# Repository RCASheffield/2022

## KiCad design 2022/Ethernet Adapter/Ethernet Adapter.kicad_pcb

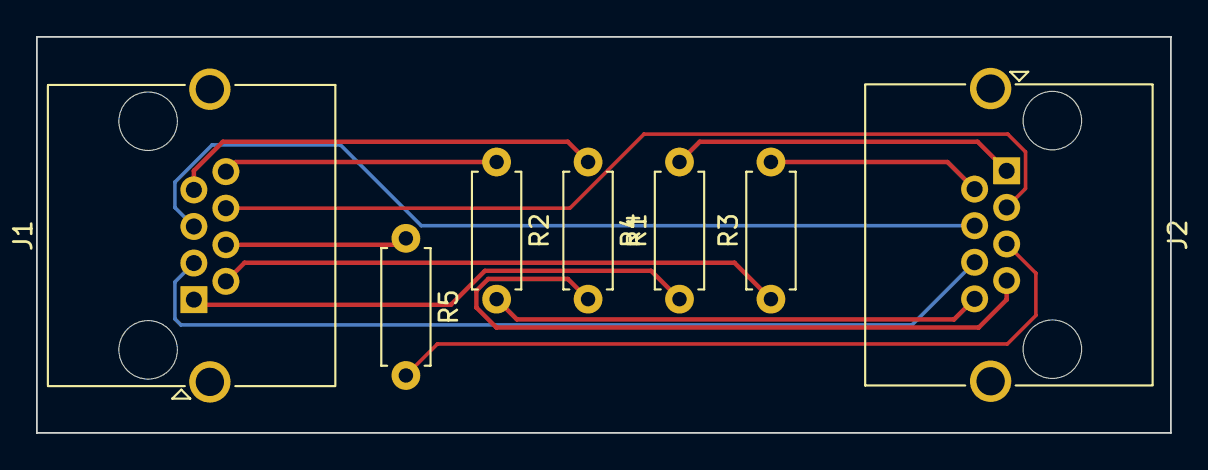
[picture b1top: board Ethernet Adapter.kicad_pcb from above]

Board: 2 copper layers, 63.0 x 22.0 mm, 7 parts (0 on the bottom side), 13 nets.

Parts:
J1, J2: Conn_01x08; RJ45_Amphenol_RJHSE5380
R1, R2, R3, R4, R5: Resistor; R_Axial_DIN0207_L6.3mm_D2.5mm_P7.62mm_Horizontal

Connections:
/GND: J2.7, R4.2
/INTERLOCK_IN: J2.2, R3.2
/INTERLOCK_RET: J2.8, R2.2
/POWER_EN: J2.1, R1.2
/RX+: J1.5, J2.4
/RX-: J2.5, R5.2
/TX+: J1.3, J2.6
/TX-: J1.6, J2.3
unnamed: J1.2, R3.1
unnamed: J1.4, R5.1
unnamed: J1.7, R4.1
unnamed: J1.8, R2.1
unnamed: J1.1, R1.1

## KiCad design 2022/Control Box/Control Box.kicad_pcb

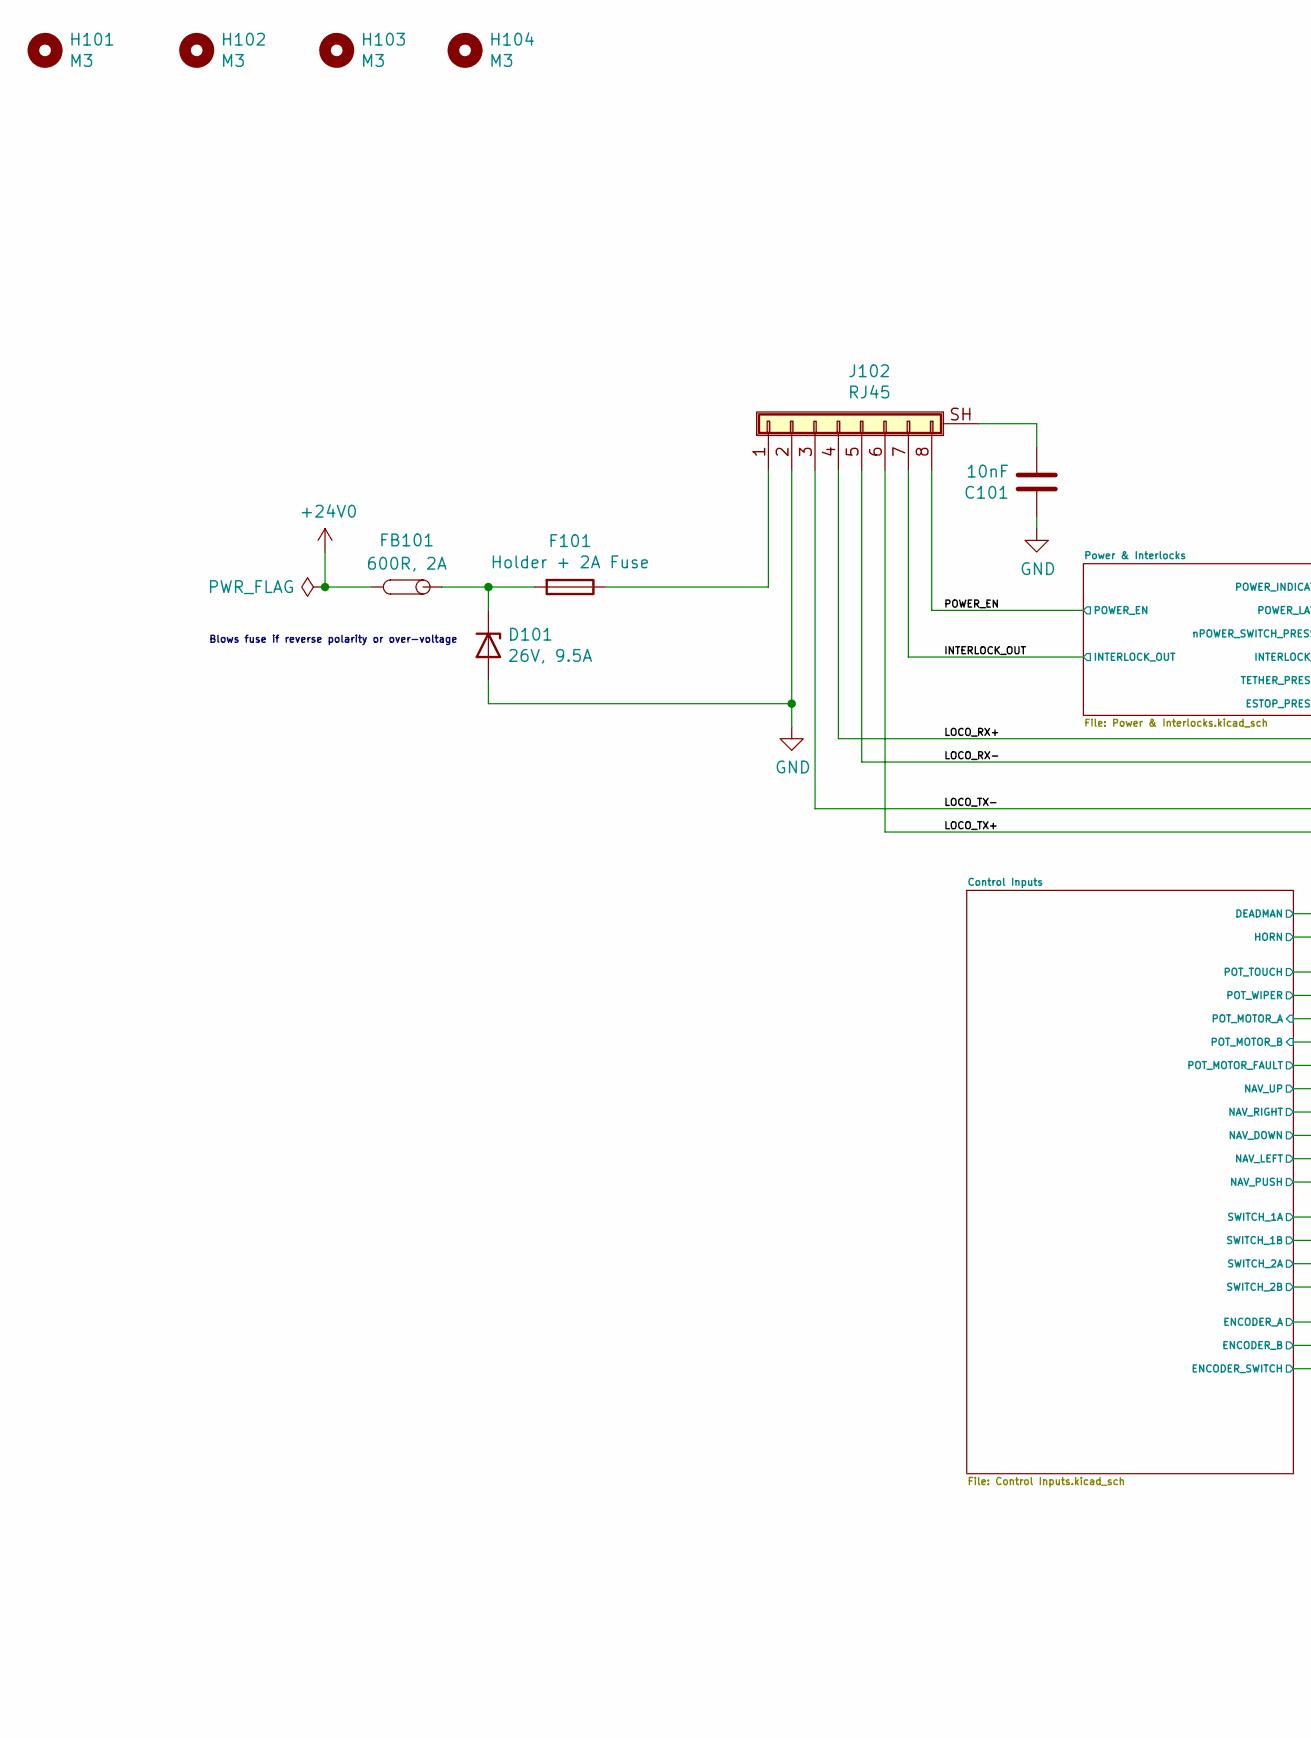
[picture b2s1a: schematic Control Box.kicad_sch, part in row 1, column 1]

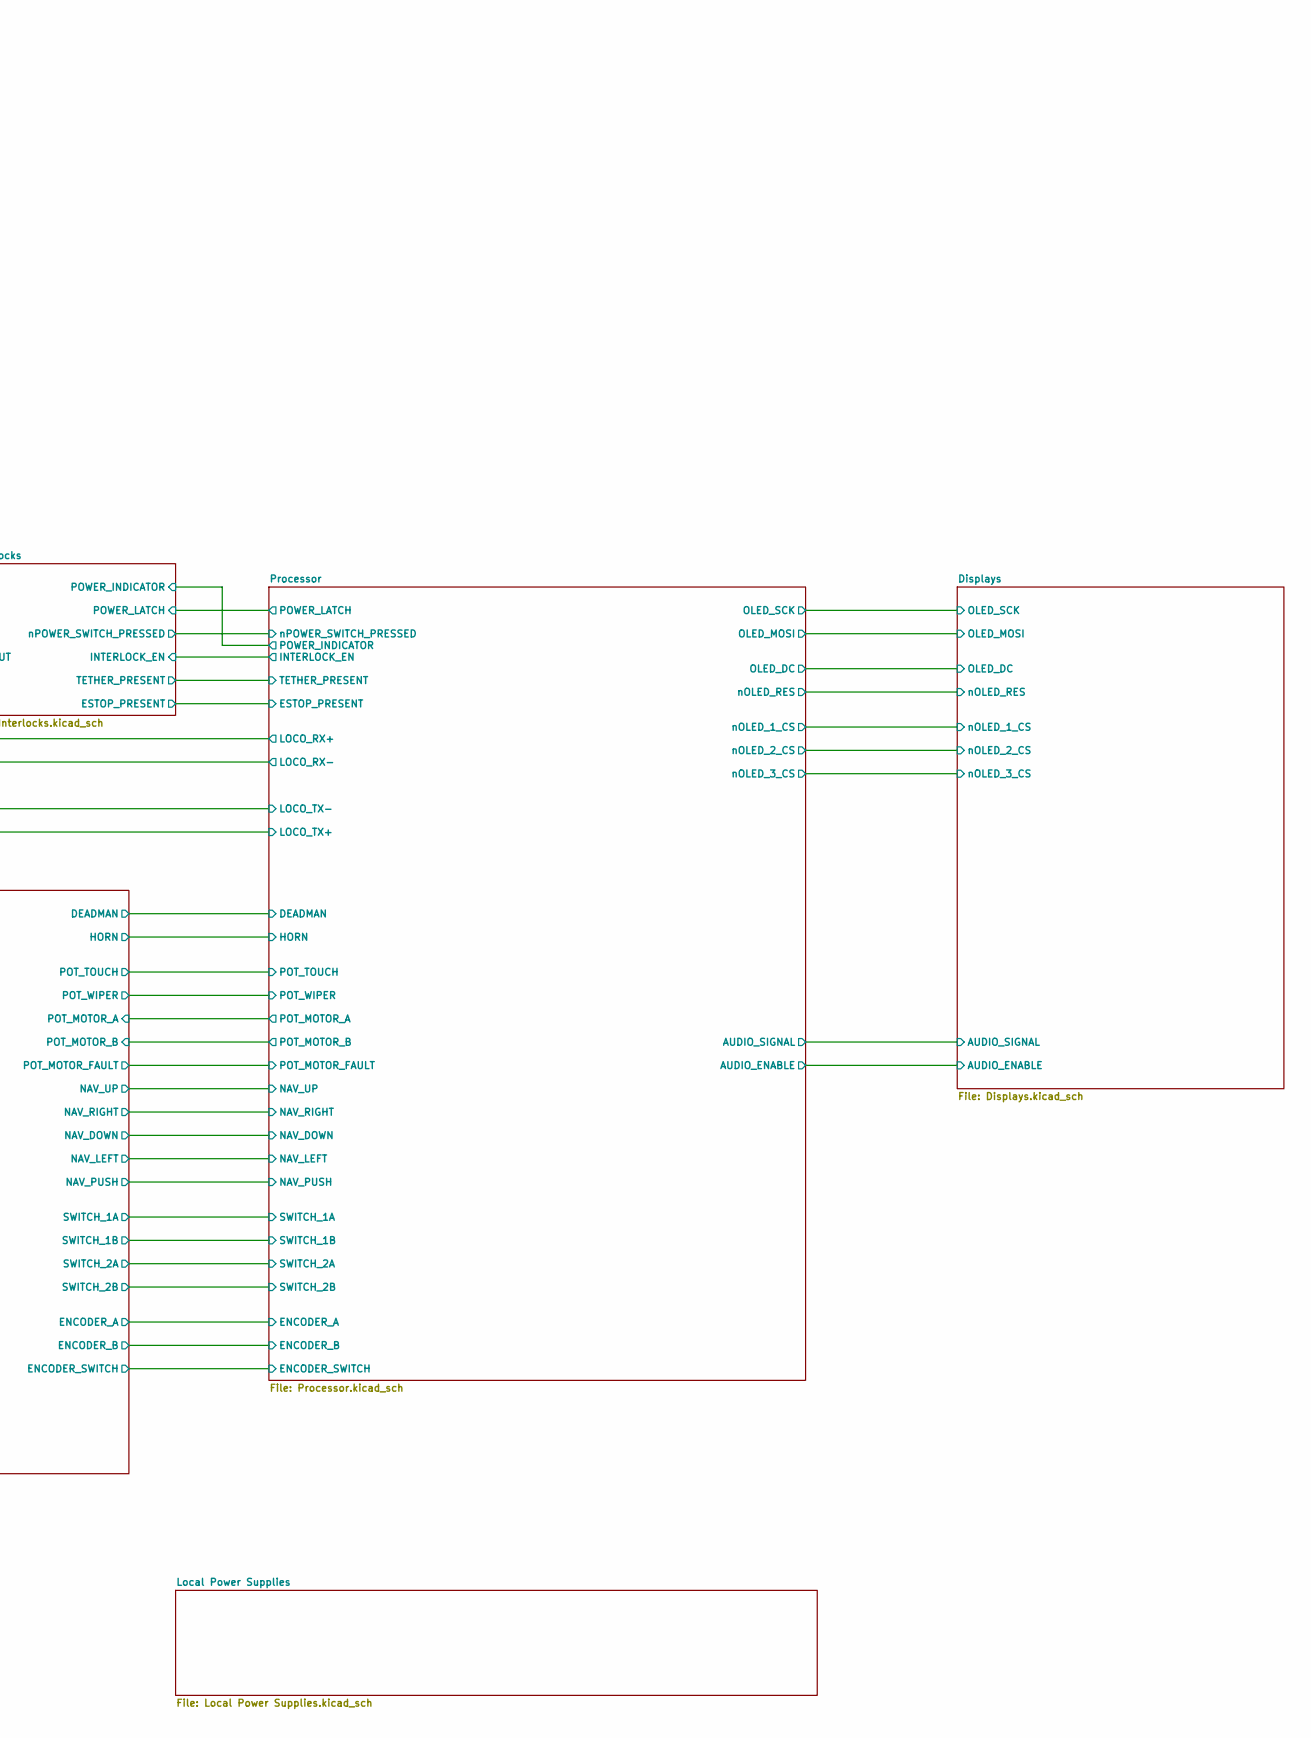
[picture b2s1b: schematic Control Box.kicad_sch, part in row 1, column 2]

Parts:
C101: 10nF; C_0603_1608Metric_Pad1.05x0.95mm_HandSolder; LCSC C57112
D101: 26V, 9.5A; D_SMA; Manufacturer Part Number SMAJ26A; LCSC C49370
F101: Holder + 2A Fuse; Fuseholder_Littelfuse_154; Manufacturer Part Number 0154002.DR
FB101: 600R, 2A; L_0805_2012Metric_Pad1.15x1.40mm_HandSolder; Manufacturer Part Number 74279220601
H101, H102, H103, H104: M3; MountingHole_3.2mm_M3
J102: RJ45; RJ45_Amphenol_RJHSE5380; Manufacturer Part Number RJHSE-5380

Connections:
+24V: FB101.2; also elsewhere on the board
/INTERLOCK_OUT: J102.7; also elsewhere on the board
/LOCO_RX+: J102.4; also elsewhere on the board
/LOCO_RX-: J102.5; also elsewhere on the board
/LOCO_TX+: J102.6; also elsewhere on the board
/LOCO_TX-: J102.3; also elsewhere on the board
/POWER_EN: J102.8; also elsewhere on the board
GND: C101.1, D101.2 (A), J102.2; also elsewhere on the board
unnamed: C101.2, J102.SH (Shield)
unnamed: D101.1 (K), F101.2, FB101.1
unnamed: F101.1, J102.1

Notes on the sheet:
Blows fuse if reverse polarity or over-voltage

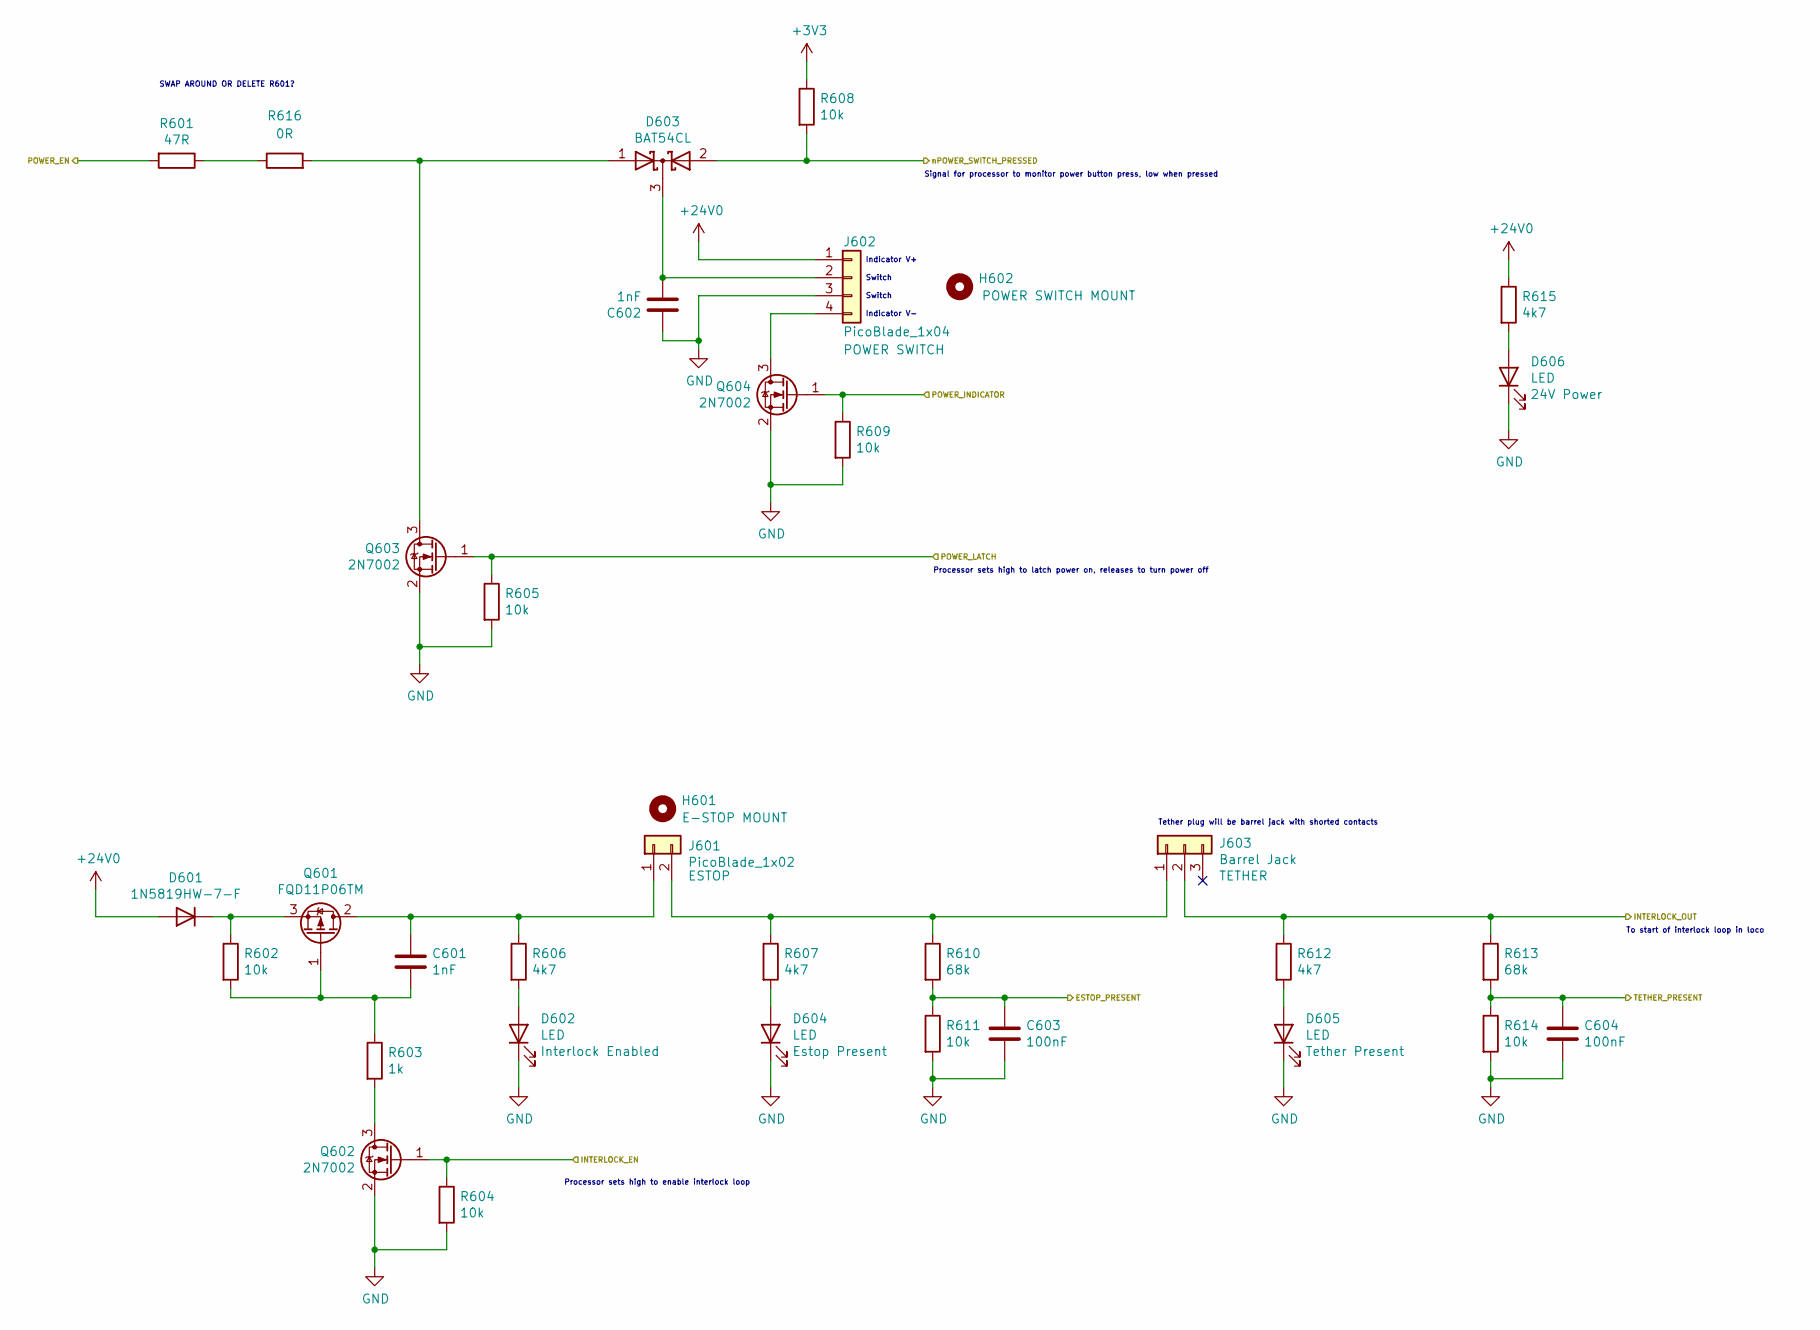
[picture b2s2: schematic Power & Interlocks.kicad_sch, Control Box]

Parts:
C601, C602: 1nF; C_0603_1608Metric_Pad1.05x0.95mm_HandSolder; LCSC C1588
C603, C604: 100nF; C_0603_1608Metric_Pad1.05x0.95mm_HandSolder; LCSC C14663
D601: 1N5819HW-7-F; D_SOD-123; Manufacturer Part Number 1N5819HW-7-F; LCSC C117948
D602, D604, D605: LED; LED_0603_1608Metric_Pad1.05x0.95mm_HandSolder; Manufacturer Part Number 150060YS75000; LCSC C205443
D603: BAT54CL; SOT-23_Handsoldering; Manufacturer Part Number BAT54CLT1G; LCSC C14308
D606: LED; LED_0603_1608Metric_Pad1.05x0.95mm_HandSolder; Manufacturer Part Number 150060VS75000; LCSC C2286
H601: 16mm Hole; 16mm_E-STOP
H602: 16mm Hole; 16mm_Power_Button
J601: PicoBlade_1x02; Molex_PicoBlade_53047-0210_1x02_P1.25mm_Vertical; Manufacturer Part Number 0530470210
J602: PicoBlade_1x04; Molex_PicoBlade_53047-0410_1x04_P1.25mm_Vertical
J603: Barrel Jack; BarrelJack_Wuerth_6941xx301002; Manufacturer Part Number 694106301002
Q601: FQD11P06TM; TO-252-2; Manufacturer Part Number FQD11P06TM; LCSC C165227
Q602, Q603, Q604: 2N7002; SOT-23_Handsoldering; Manufacturer Part Number 2N7002,215; LCSC C239589
R601: 47R; R_0603_1608Metric_Pad1.05x0.95mm_HandSolder; LCSC C23182
R602, R604, R605, R608, R609: 10k; R_0603_1608Metric_Pad1.05x0.95mm_HandSolder; LCSC C25804
R603: 1k; R_0603_1608Metric_Pad1.05x0.95mm_HandSolder; LCSC C21190
R606, R607, R612, R615: 4k7; R_0603_1608Metric_Pad1.05x0.95mm_HandSolder; LCSC C23162
R610, R613: 68k; R_0603_1608Metric_Pad1.05x0.95mm_HandSolder; LCSC C25804
R611, R614: 10k; R_0603_1608Metric_Pad1.05x0.95mm_HandSolder; LCSC C23231
R616: 0R

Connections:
+3V3: R608.1; also elsewhere on the board
+24V: D601.2 (A), J602.1, R615.1; also elsewhere on the board
/INTERLOCK_OUT: J603.2, R612.1, R613.1; also elsewhere on the board
/POWER_EN: R601.2; also elsewhere on the board
/Power & Interlocks/ESTOP_PRESENT: C603.1, R610.2, R611.1; also elsewhere on the board
/Power & Interlocks/INTERLOCK_EN: Q602.1 (G), R604.1; also elsewhere on the board
/Power & Interlocks/POWER_INDICATOR: Q604.1 (G), R609.1; also elsewhere on the board
/Power & Interlocks/POWER_LATCH: Q603.1 (G), R605.1; also elsewhere on the board
/Power & Interlocks/TETHER_PRESENT: C604.1, R613.2, R614.1; also elsewhere on the board
/Power & Interlocks/nPOWER_SWITCH_PRESSED: D603.2 (A), R608.2; also elsewhere on the board
GND: C602.1, C603.2, C604.2, D602.1 (K), D604.1 (K), D605.1 (K), D606.1 (K), J602.3, Q602.2 (S), Q603.2 (S), Q604.2 (S), R604.2, R605.2, R609.2, R611.2, R614.2; also elsewhere on the board
unnamed: C601.1, J601.1, Q601.2 (D), R606.1
unnamed: C601.2, Q601.1 (G), R602.2, R603.1
unnamed: C602.2, D603.3 (K), J602.2
unnamed: D601.1 (K), Q601.3 (S), R602.1
unnamed: D602.2 (A), R606.2
unnamed: D604.2 (A), R607.2
unnamed: D605.2 (A), R612.2
unnamed: D606.2 (A), R615.2
unnamed: J601.2, J603.1, R607.1, R610.1
unnamed: J602.4, Q604.3 (D)
unnamed: Q602.3 (D), R603.2

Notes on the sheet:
Switch
Processor sets high to enable interlock loop
To start of interlock loop in loco
SWAP AROUND OR DELETE R601?
Indicator V-
Processor sets high to latch power on, releases to turn power off
Signal for processor to monitor power button press, low when pressed
Tether plug will be barrel jack with shorted contacts
Indicator V+

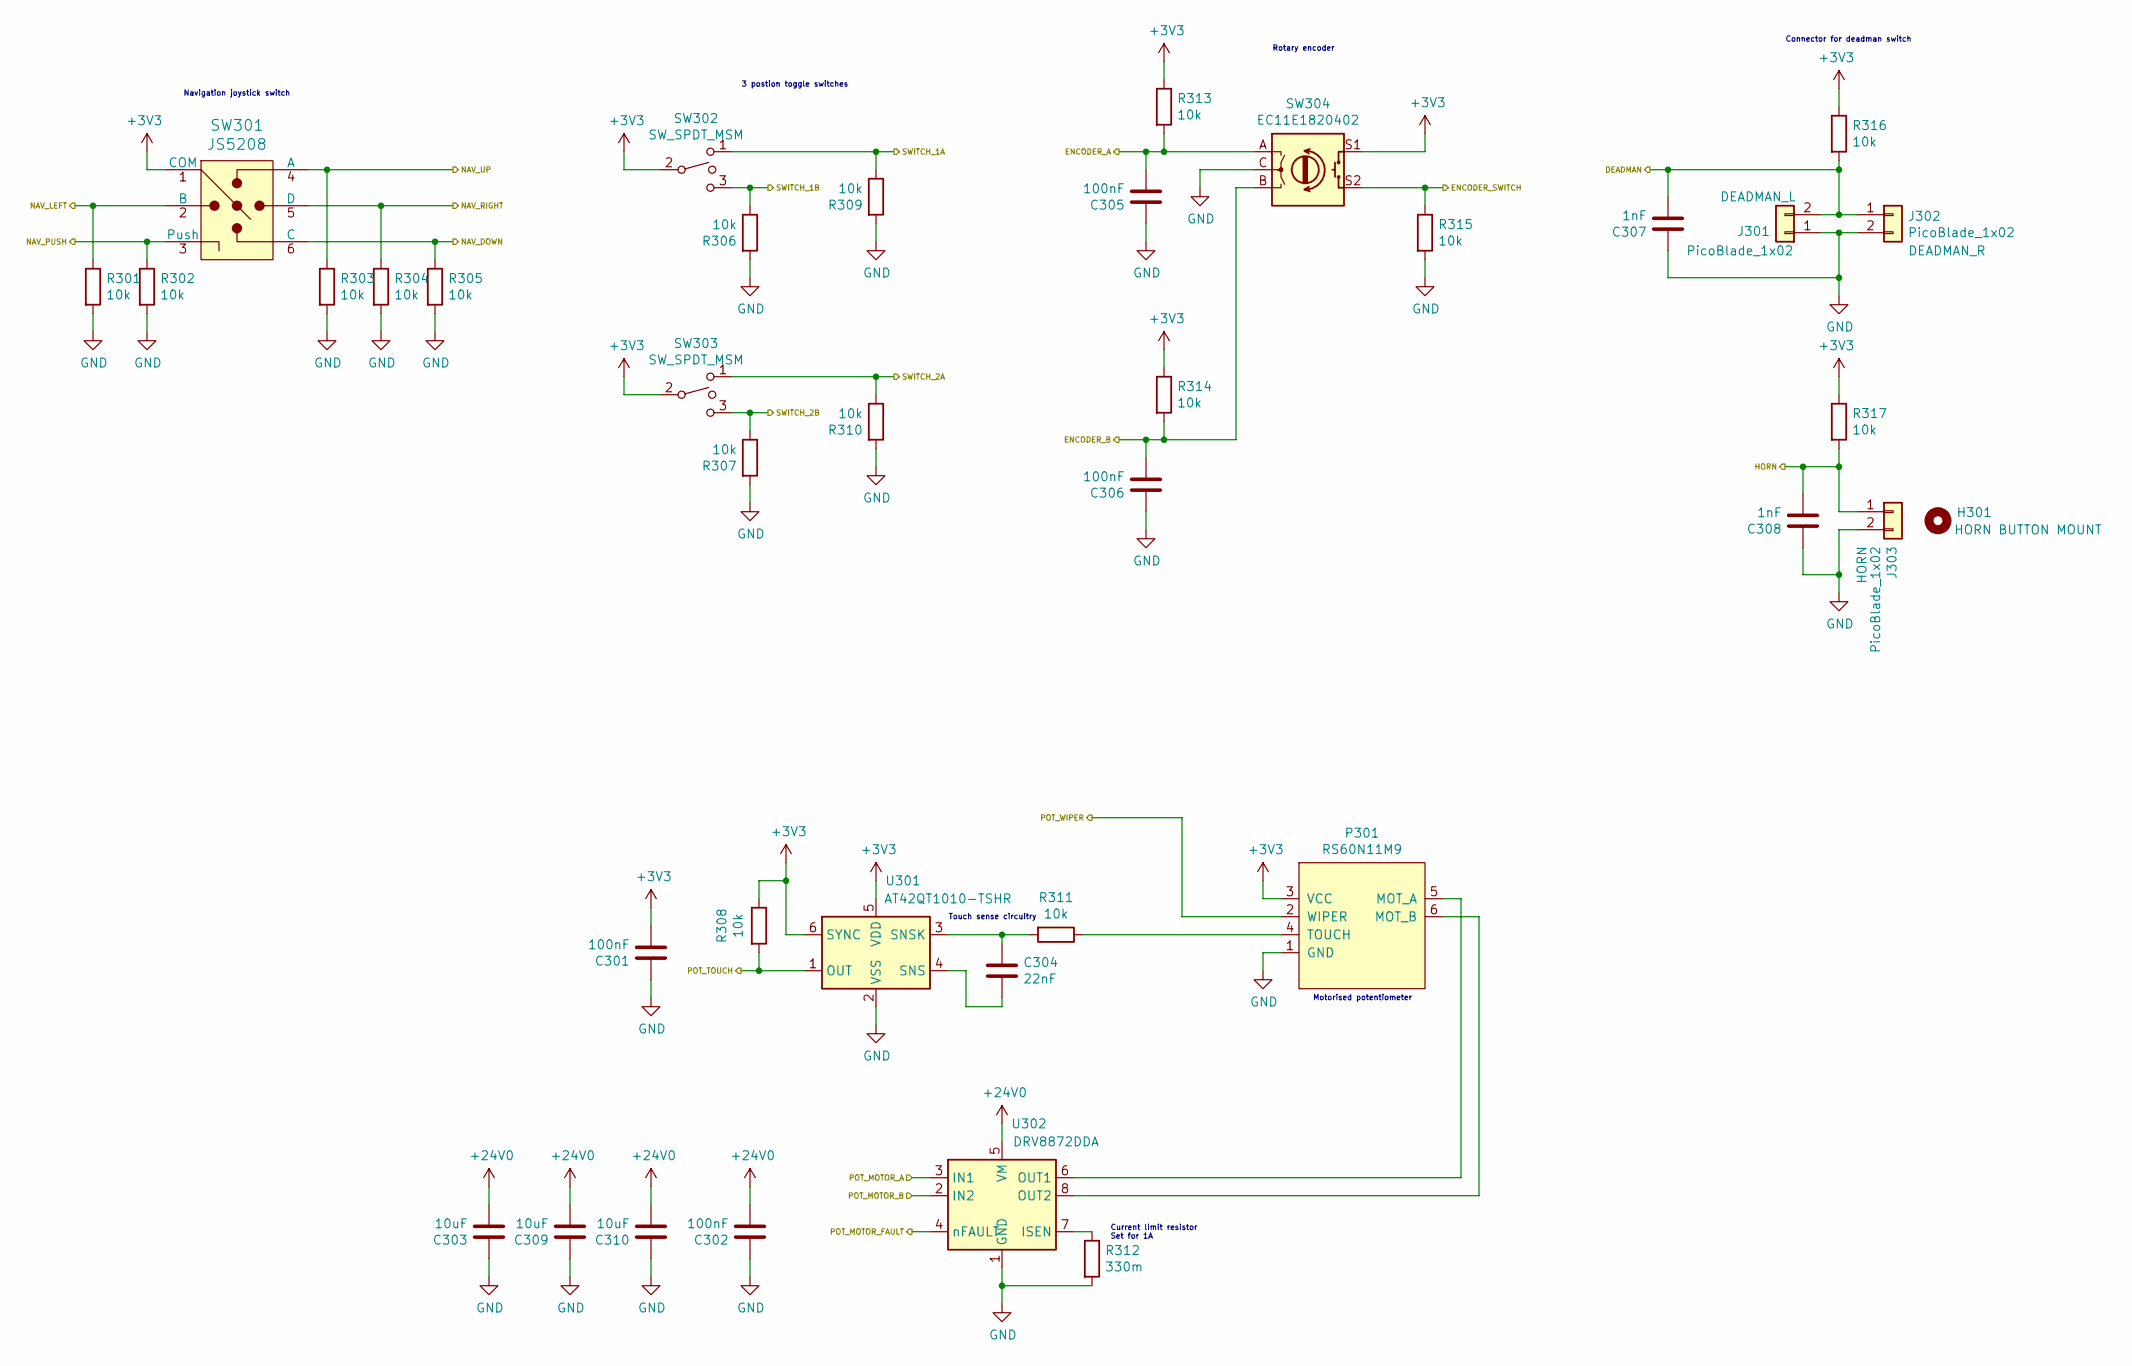
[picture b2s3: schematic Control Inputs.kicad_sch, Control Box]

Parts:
C301, C302, C305, C306: 100nF; C_0603_1608Metric_Pad1.05x0.95mm_HandSolder; LCSC C14663
C303, C309, C310: 10uF; C_1210_3225Metric_Pad1.42x2.65mm_HandSolder; LCSC C39232
C304: 22nF; C_0603_1608Metric_Pad1.05x0.95mm_HandSolder; LCSC C21122
C307, C308: 1nF; C_0603_1608Metric_Pad1.05x0.95mm_HandSolder; LCSC C1588
H301: 16mm Hole; 16mm_Blank_Button
J301, J302, J303: PicoBlade_1x02; Molex_PicoBlade_53047-0210_1x02_P1.25mm_Vertical; Manufacturer Part Number 0530470210
P301: RS60N11M9; Potentiometer_Motorised_RS60N11M9
R301, R302, R303, R304, R305, R306, R307, R308, R309, R310, R311, R313, R314, R315, R316, R317: 10k; R_0603_1608Metric_Pad1.05x0.95mm_HandSolder; LCSC C25804
R312: 330m; R_1210_3225Metric_Pad1.42x2.65mm_HandSolder; LCSC C127712
SW301: JS5208; Switch_Nav_12.4x12.4mm
SW302, SW303: SW_SPDT_MSM; SW_Toggle_14x7mm
SW304: EC11E1820402; RotaryEncoder_Alps_EC11E-Switch_Vertical_H20mm
U301: AT42QT1010-TSHR; SOT-23-6; LCSC C74512
U302: DRV8872DDA; Texas_HTSOP-8-1EP_3.9x4.9mm_P1.27mm_EP2.95x4.9mm_Mask2.4x3.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; LCSC C114179

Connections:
+3V3: C301.2, P301.3 (VCC), R308.1, R313.1, R314.1, R316.1, R317.1, SW301.1 (COM), SW302.2, SW303.2, SW304.S1, U301.5 (VDD), U301.6 (SYNC); also elsewhere on the board
+24V: C302.2, C303.1, C309.1, C310.1, U302.5 (VM); also elsewhere on the board
/Control Inputs/DEADMAN: C307.2, J301.2, J302.1, R316.2; also elsewhere on the board
/Control Inputs/ENCODER_A: C305.2, R313.2, SW304.A; also elsewhere on the board
/Control Inputs/ENCODER_B: C306.2, R314.2, SW304.B; also elsewhere on the board
/Control Inputs/ENCODER_SWITCH: R315.1, SW304.S2; also elsewhere on the board
/Control Inputs/HORN: C308.2, J303.1, R317.2; also elsewhere on the board
/Control Inputs/NAV_DOWN: R305.1, SW301.6 (C); also elsewhere on the board
/Control Inputs/NAV_LEFT: R301.1, SW301.2 (B); also elsewhere on the board
/Control Inputs/NAV_PUSH: R302.1, SW301.3 (Push); also elsewhere on the board
/Control Inputs/NAV_RIGHT: R304.1, SW301.5 (D); also elsewhere on the board
/Control Inputs/NAV_UP: R303.1, SW301.4 (A); also elsewhere on the board
/Control Inputs/POT_MOTOR_A: U302.3 (IN1); also elsewhere on the board
/Control Inputs/POT_MOTOR_B: U302.2 (IN2); also elsewhere on the board
/Control Inputs/POT_MOTOR_FAULT: U302.4 (nFAULT); also elsewhere on the board
/Control Inputs/POT_TOUCH: R308.2, U301.1 (OUT); also elsewhere on the board
/Control Inputs/POT_WIPER: P301.2 (WIPER); also elsewhere on the board
/Control Inputs/SWITCH_1A: R309.1, SW302.1; also elsewhere on the board
/Control Inputs/SWITCH_1B: R306.1, SW302.3; also elsewhere on the board
/Control Inputs/SWITCH_2A: R310.1, SW303.1; also elsewhere on the board
/Control Inputs/SWITCH_2B: R307.1, SW303.3; also elsewhere on the board
GND: C301.1, C302.1, C303.2, C305.1, C306.1, C307.1, C308.1, C309.2, C310.2, J301.1, J302.2, J303.2, P301.1 (GND), R301.2, R302.2, R303.2, R304.2, R305.2, R306.2, R307.2, R309.2, R310.2, R312.2, R315.2, SW304.C, U301.2 (VSS), U302.1 (GND), U302.9 (GND); also elsewhere on the board
unnamed: C304.1, R311.2, U301.3 (SNSK)
unnamed: C304.2, U301.4 (SNS)
unnamed: P301.4 (TOUCH), R311.1
unnamed: P301.5 (MOT_A), U302.6 (OUT1)
unnamed: P301.6 (MOT_B), U302.8 (OUT2)
unnamed: R312.1, U302.7 (ISEN)

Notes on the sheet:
Connector for deadman switch
Motorised potentiometer
Touch sense circuitry
Current limit resistor Set for 1A
Navigation joystick switch
Rotary encoder
3 postion toggle switches

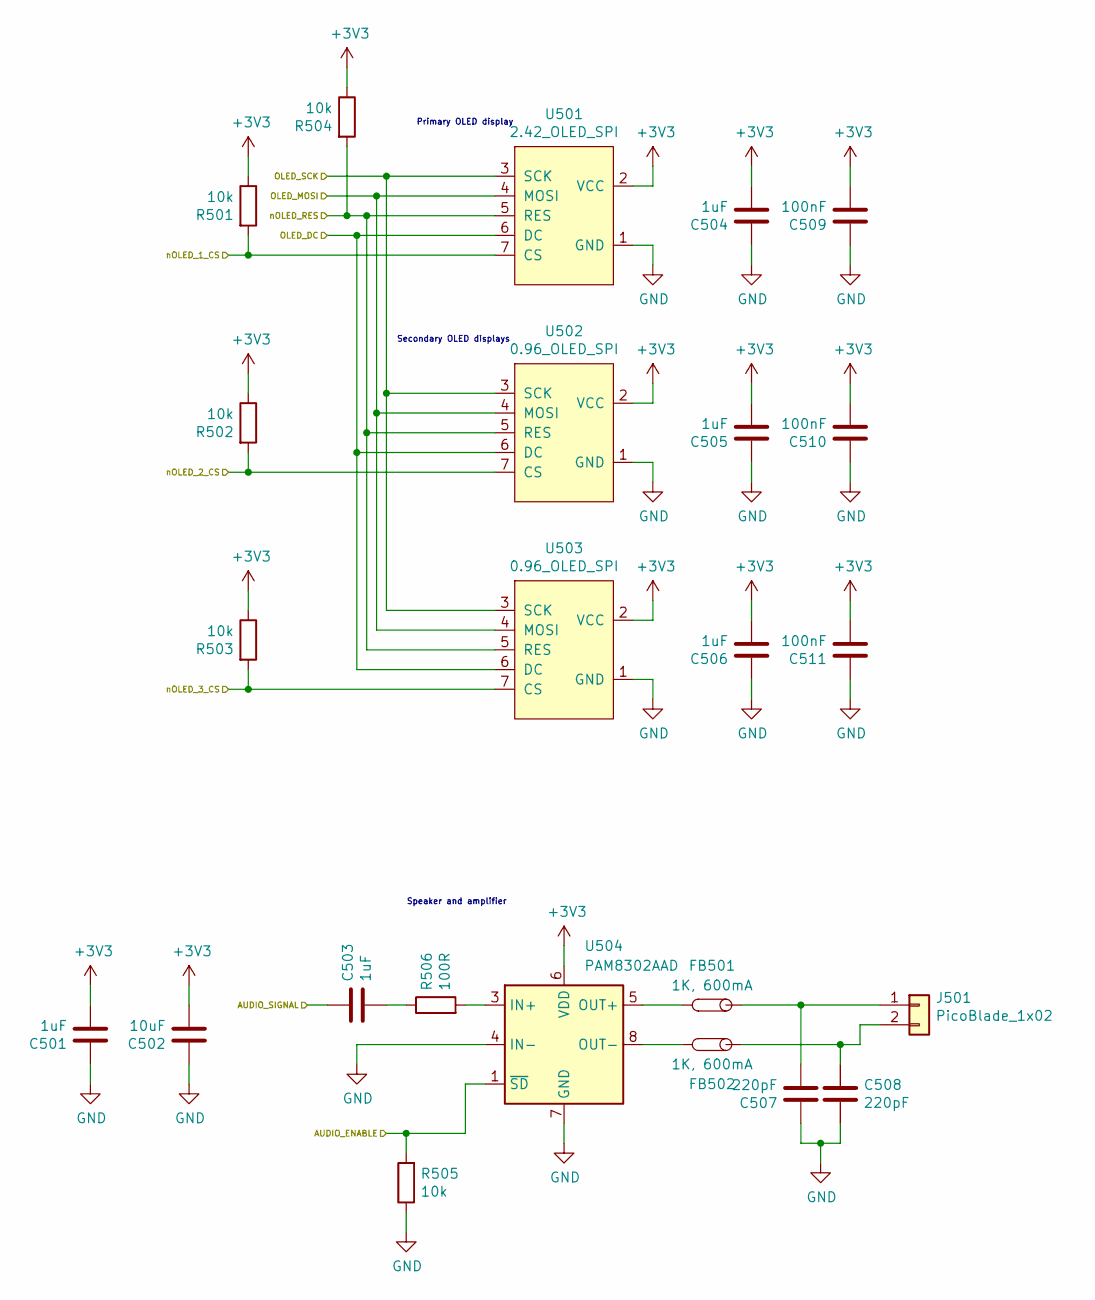
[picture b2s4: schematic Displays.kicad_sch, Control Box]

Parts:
C501, C503, C504, C505, C506: 1uF; C_0603_1608Metric_Pad1.05x0.95mm_HandSolder; LCSC C15849
C502: 10uF; C_0603_1608Metric_Pad1.05x0.95mm_HandSolder; LCSC C19702
C507, C508: 220pF; C_0603_1608Metric_Pad1.05x0.95mm_HandSolder; LCSC C1603
C509, C510, C511: 100nF; C_0603_1608Metric_Pad1.05x0.95mm_HandSolder; LCSC C14663
FB501, FB502: 1K, 600mA; L_0603_1608Metric_Pad1.05x0.95mm_HandSolder; Manufacturer Part Number 742792662; LCSC C85824
J501: PicoBlade_1x02; Molex_PicoBlade_53047-0210_1x02_P1.25mm_Vertical; Manufacturer Part Number 0530470210
R501, R502, R503, R504, R505: 10k; R_0603_1608Metric_Pad1.05x0.95mm_HandSolder; LCSC C25804
R506: 100R; R_0603_1608Metric_Pad1.05x0.95mm_HandSolder; LCSC C22775
U501: 2.42_OLED_SPI; 2.42_OLED; Manufacturer Part Number D030526BA
U502, U503: 0.96_OLED_SPI; 0.96_OLED; Manufacturer Part Number 2453559
U504: PAM8302AAD; MSOP-8_3x3mm_P0.65mm; LCSC C112137

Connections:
+3V3: C501.2, C502.2, C504.2, C505.2, C506.2, C509.2, C510.2, C511.2, R501.1, R502.1, R503.1, R504.1, U501.2 (VCC), U502.2 (VCC), U503.2 (VCC), U504.6 (VDD); also elsewhere on the board
/Displays/AUDIO_ENABLE: R505.2, U504.1 (~SD); also elsewhere on the board
/Displays/AUDIO_SIGNAL: C503.1; also elsewhere on the board
/Displays/OLED_DC: U501.6 (DC), U502.6 (DC), U503.6 (DC); also elsewhere on the board
/Displays/OLED_MOSI: U501.4 (MOSI), U502.4 (MOSI), U503.4 (MOSI); also elsewhere on the board
/Displays/OLED_SCK: U501.3 (SCK), U502.3 (SCK), U503.3 (SCK); also elsewhere on the board
/Displays/nOLED_1_CS: R501.2, U501.7 (CS); also elsewhere on the board
/Displays/nOLED_2_CS: R502.2, U502.7 (CS); also elsewhere on the board
/Displays/nOLED_3_CS: R503.2, U503.7 (CS); also elsewhere on the board
/Displays/nOLED_RES: R504.2, U501.5 (RES), U502.5 (RES), U503.5 (RES); also elsewhere on the board
GND: C501.1, C502.1, C504.1, C505.1, C506.1, C507.1, C508.2, C509.1, C510.1, C511.1, R505.1, U501.1 (GND), U502.1 (GND), U503.1 (GND), U504.4 (IN-), U504.7 (GND); also elsewhere on the board
unnamed: C503.2, R506.1
unnamed: C507.2, FB501.1, J501.1
unnamed: C508.1, FB502.1, J501.2
unnamed: FB501.2, U504.5 (OUT+)
unnamed: FB502.2, U504.8 (OUT-)
unnamed: R506.2, U504.3 (IN+)

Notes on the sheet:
Primary OLED display
Secondary OLED displays
Speaker and amplifier

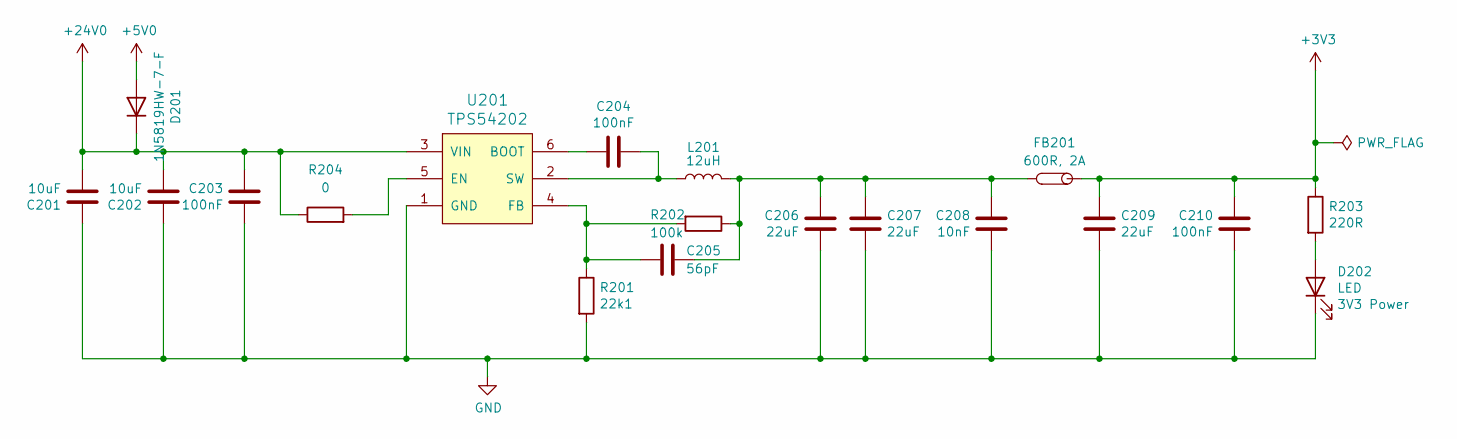
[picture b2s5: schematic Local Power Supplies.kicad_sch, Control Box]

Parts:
C201, C202: 10uF; C_1210_3225Metric_Pad1.42x2.65mm_HandSolder; LCSC C39232
C203, C204, C210: 100nF; C_0603_1608Metric_Pad1.05x0.95mm_HandSolder; LCSC C14663
C205: 56pF; C_0603_1608Metric_Pad1.05x0.95mm_HandSolder; LCSC C39148
C206, C207, C209: 22uF; C_1206_3216Metric_Pad1.42x1.75mm_HandSolder; LCSC C12891
C208: 10nF; C_0603_1608Metric_Pad1.05x0.95mm_HandSolder; LCSC C57112
D201: 1N5819HW-7-F; D_SOD-123; Manufacturer Part Number 1N5819HW-7-F; LCSC C117948
D202: LED; LED_0603_1608Metric_Pad1.05x0.95mm_HandSolder; Manufacturer Part Number 150060VS75000; LCSC C2286
FB201: 600R, 2A; L_0805_2012Metric_Pad1.15x1.40mm_HandSolder; Manufacturer Part Number 74279220601
L201: 12uH; L_6.3x6.3_H3; LCSC C324292
R201: 22k1; R_0603_1608Metric_Pad1.05x0.95mm_HandSolder; LCSC C31850
R202: 100k; R_0603_1608Metric_Pad1.05x0.95mm_HandSolder; LCSC C25803
R203: 220R; R_0603_1608Metric_Pad1.05x0.95mm_HandSolder; LCSC C22962
R204: 0; R_0201_0603Metric
U201: TPS54202; SOT-23-6_Handsoldering; LCSC C134129

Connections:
+3V3: C209.1, C210.2, FB201.1, R203.1; also elsewhere on the board
+5V: D201.2 (A); also elsewhere on the board
+24V: C201.1, C202.1, C203.2, D201.1 (K), R204.1, U201.3 (VIN); also elsewhere on the board
GND: C201.2, C202.2, C203.1, C206.2, C207.2, C208.1, C209.2, C210.1, D202.1 (K), R201.2, U201.1 (GND); also elsewhere on the board
unnamed: C204.1, L201.1, U201.2 (SW)
unnamed: C204.2, U201.6 (BOOT)
unnamed: C205.1, R201.1, R202.2, U201.4 (FB)
unnamed: C205.2, C206.1, C207.1, C208.2, FB201.2, L201.2, R202.1
unnamed: D202.2 (A), R203.2
unnamed: R204.2, U201.5 (EN)

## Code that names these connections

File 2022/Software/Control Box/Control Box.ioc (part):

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Mcu.Name=STM32F405VGTx
Mcu.Package=LQFP100
Mcu.UserName=STM32F405VGTx
PA10.GPIOParameters=GPIO_Label
PA10.GPIO_Label=DEBUG_RX
PA10.Mode=Asynchronous
PA10.Signal=USART1_RX
PA2.GPIOParameters=GPIO_Label
PA2.GPIO_Label=LOCO_TX
PA2.Mode=Asynchronous
PA2.Signal=USART2_TX
PA3.GPIOParameters=GPIO_Label
PA3.GPIO_Label=LOCO_RX
PA3.Mode=Asynchronous
PA3.Signal=USART2_RX
PA4.GPIOParameters=PinState,GPIO_PuPd,GPIO_Label
PA4.GPIO_Label=OLED_1_CS
PA4.GPIO_PuPd=GPIO_NOPULL
PA4.PinState=GPIO_PIN_SET
PA4.Signal=GPIO_Output
PA5.Mode=TX_Only_Simplex_Unidirect_Master
PA5.Signal=SPI1_SCK
PA6.GPIOParameters=GPIO_PuPd,GPIO_Label
PA6.GPIO_Label=OLED_RES
PA6.GPIO_PuPd=GPIO_NOPULL
PA6.Signal=GPIO_Output
PA7.Mode=TX_Only_Simplex_Unidirect_Master
PA7.Signal=SPI1_MOSI
PA9.GPIOParameters=GPIO_Label
PA9.GPIO_Label=DEBUG_TX
PA9.Mode=Asynchronous
PA9.Signal=USART1_TX
PB0.GPIOParameters=GPIO_Label
PB0.GPIO_Label=POT_WIPER
PB0.Signal=SharedAnalog_PB0
PB1.GPIOParameters=GPIO_Label
PB1.GPIO_Label=POT_MOTOR_FAULT
PB1.Signal=GPIO_Input
PB4.GPIOParameters=GPIO_Label
PB4.GPIO_Label=POT_MOT_A
PB4.Signal=S_TIM3_CH1
PB5.GPIOParameters=GPIO_Label
PB5.GPIO_Label=POT_MOT_B
PB5.Signal=S_TIM3_CH2
PB6.GPIOParameters=GPIO_Label
PB6.GPIO_Label=OLED_3_CS
PB6.Signal=GPIO_Output
PB7.GPIOParameters=GPIO_Label
PB7.GPIO_Label=OLED_2_CS
PB7.Signal=GPIO_Output
PB9.GPIOParameters=GPIO_Label
PB9.GPIO_Label=OLED_DC
PB9.Signal=GPIO_Output
PC0.GPIOParameters=GPIO_Label
PC0.GPIO_Label=SWITCH_1A
PC0.Signal=GPIO_Input
PC1.GPIOParameters=GPIO_Label
PC1.GPIO_Label=SWITCH_1B
PC1.Signal=GPIO_Input
PC2.GPIOParameters=GPIO_Label
PC2.GPIO_Label=SWITCH_2A
PC2.Signal=GPIO_Input
PC3.GPIOParameters=GPIO_Label
PC3.GPIO_Label=SWITCH_2B
PC3.Signal=GPIO_Input
PC4.GPIOParameters=GPIO_Label
PC4.GPIO_Label=LED_1
PC4.Signal=GPIO_Output
PC5.GPIOParameters=GPIO_Label
PC5.GPIO_Label=LED_2
PC5.Signal=GPIO_Output
PC6.GPIOParameters=GPIO_Label
PC6.GPIO_Label=ENCODER_B
PC6.Signal=S_TIM8_CH1
PC7.GPIOParameters=GPIO_Label
PC7.GPIO_Label=ENCODER_A
PC7.Signal=S_TIM8_CH2
PC8.GPIOParameters=GPIO_Label
PC8.GPIO_Label=ENCODER_SWITCH
PC8.Signal=GPIO_Input
PD0.GPIOParameters=GPIO_Label
PD0.GPIO_Label=nPOWER_SWITCH_PRESSED
PD0.Signal=GPIO_Input
PD1.GPIOParameters=GPIO_Label
PD1.GPIO_Label=POWER_LATCH
PD1.Signal=GPIO_Output
PD2.GPIOParameters=PinState,GPIO_Label
PD2.GPIO_Label=INTERLOCK_EN
PD2.PinState=GPIO_PIN_RESET
PD2.Signal=GPIO_Output
PD3.GPIOParameters=GPIO_Label
PD3.GPIO_Label=ESTOP_PRESENT
PD3.Signal=GPIO_Input
PD4.GPIOParameters=GPIO_Label
PD4.GPIO_Label=TETHER_PRESENT
PD4.Signal=GPIO_Input
PD5.GPIOParameters=GPIO_Label
PD5.GPIO_Label=POWER_INDICATOR
PD5.Signal=GPIO_Output
PE0.GPIOParameters=GPIO_Label
PE0.GPIO_Label=DEADMAN
PE0.Signal=GPIO_Input
PE1.GPIOParameters=GPIO_Label
PE1.GPIO_Label=nHORN_PRESSED
PE1.Signal=GPIO_Input
RCC.HSE_VALUE=25000000
RCC.SYSCLKFreq_VALUE=64000000
RCC.SYSCLKSource=RCC_SYSCLKSOURCE_PLLCLK
board=custom

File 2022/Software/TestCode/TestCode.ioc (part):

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Mcu.Name=STM32F103R(8-B)Tx
Mcu.Package=LQFP64
Mcu.UserName=STM32F103RBTx
PA0-WKUP.GPIOParameters=GPIO_Label
PA0-WKUP.GPIO_Label=AMBIENT_TEMP
PA0-WKUP.Signal=ADCx_IN0
PA1.GPIOParameters=GPIO_Label
PA1.GPIO_Label=LOCO_TX_ENABLE
PA1.Signal=GPIO_Output
PA10.GPIOParameters=GPIO_Label
PA10.GPIO_Label=INDEX
PA10.Signal=GPXTI10
PA13.GPIOParameters=GPIO_Label
PA13.GPIO_Label=TMS
PA13.Mode=Serial_Wire
PA13.Signal=SYS_JTMS-SWDIO
PA14.GPIOParameters=GPIO_Label
PA14.GPIO_Label=TCK
PA14.Mode=Serial_Wire
PA14.Signal=SYS_JTCK-SWCLK
PA2.GPIOParameters=GPIO_Speed,GPIO_PuPd,GPIO_Label,GPIO_Mode
PA2.GPIO_Label=LOCO_TX
PA2.GPIO_Mode=GPIO_MODE_AF_PP
PA2.GPIO_PuPd=GPIO_NOPULL
PA2.GPIO_Speed=GPIO_SPEED_FREQ_LOW
PA2.Mode=Asynchronous
PA2.Signal=USART2_TX
PA3.GPIOParameters=GPIO_Speed,GPIO_PuPd,GPIO_Label,GPIO_Mode
PA3.GPIO_Label=LOCO_RX
PA3.GPIO_Mode=GPIO_MODE_AF_PP
PA3.GPIO_PuPd=GPIO_NOPULL
PA3.GPIO_Speed=GPIO_SPEED_FREQ_LOW
PA3.Mode=Asynchronous
PA3.Signal=USART2_RX
PA4.GPIOParameters=GPIO_Label
PA4.GPIO_Label=MONITORING_24V
PA4.Signal=ADCx_IN4
PA5.GPIOParameters=GPIO_Speed,GPIO_PuPd,GPIO_Label,GPIO_ModeDefaultOutputPP
PA5.GPIO_Label=LD2 [Green Led]
PA5.GPIO_ModeDefaultOutputPP=GPIO_MODE_OUTPUT_PP
PA5.GPIO_PuPd=GPIO_NOPULL
PA5.GPIO_Speed=GPIO_SPEED_FREQ_LOW
PA5.Signal=GPIO_Output
PA6.Signal=S_TIM3_CH1
PA7.Signal=S_TIM3_CH2
PA8.GPIOParameters=GPIO_Label
PA8.GPIO_Label=CH_A
PA8.Signal=S_TIM1_CH1
PA9.GPIOParameters=GPIO_Label
PA9.GPIO_Label=CH_B
PA9.Signal=S_TIM1_CH2
PB0.GPIOParameters=GPIO_Label
PB0.GPIO_Label=WS2812
PB0.Signal=S_TIM3_CH3
PB1.GPIOParameters=GPIO_Label
PB1.GPIO_Label=ISOLATED_INPUT_UPDATED
PB1.Signal=GPXTI1
PB10.Mode=I2C
PB10.Signal=I2C2_SCL
PB11.Mode=I2C
PB11.Signal=I2C2_SDA
PB3.Signal=SYS_JTDO-TRACESWO
PB5.GPIOParameters=GPIO_Label
PB5.GPIO_Label=nBODYWORK_CLOSED
PB5.Signal=GPXTI5
PB8.Mode=CAN_Activate
PB8.Signal=CAN_RX
PB9.Mode=CAN_Activate
PB9.Signal=CAN_TX
PC0.GPIOParameters=GPIO_Label
PC0.GPIO_Label=VINT_PRESENT
PC0.Signal=GPIO_Input
PC1.GPIOParameters=GPIO_Label
PC1.GPIO_Label=ESTOP2_PRESENT
PC1.Signal=GPIO_Input
PC10.GPIOParameters=GPIO_Label
PC10.GPIO_Label=RELAY_SELECT
PC10.Signal=GPIO_Output
PC11.GPIOParameters=GPIO_Label
PC11.GPIO_Label=RELAY_OVERCURRENT
PC11.Signal=GPIO_Input
PC12.GPIOParameters=GPIO_Label
PC12.GPIO_Label=RELAY_UNDERCURRENT
PC12.Signal=GPIO_Input
PC13-TAMPER-RTC.GPIOParameters=GPIO_Label
PC13-TAMPER-RTC.GPIO_Label=VARIANT_INDICATOR
PC13-TAMPER-RTC.Signal=GPIO_Input
PC14-OSC32_IN.Signal=RCC_OSC32_IN
PC15-OSC32_OUT.Signal=RCC_OSC32_OUT
PC2.GPIOParameters=GPIO_Label
PC2.GPIO_Label=ESTOP1_PRESENT
PC2.Signal=GPIO_Input
PC3.GPIOParameters=GPIO_Label
PC3.GPIO_Label=INTERLOCK_IN_PRESENT
PC3.Signal=GPIO_Input
PC4.GPIOParameters=GPIO_Label
PC4.GPIO_Label=CLOSE_INTERLOCK_TRIGGER
PC4.Signal=GPIO_Output
PC5.GPIOParameters=GPIO_Label
PC5.GPIO_Label=HORN_CONTROL
PC5.Signal=GPIO_Output
PC6.GPIOParameters=GPIO_Label
PC6.GPIO_Label=BRAKE_CONTROL
PC6.Signal=GPIO_Output
PC7.GPIOParameters=GPIO_Label
PC7.GPIO_Label=BRAKE_OVERCURRENT
PC7.Signal=GPIO_Input
PC8.GPIOParameters=GPIO_Label
PC8.GPIO_Label=BRAKE_UNDERCURRENT
PC8.Signal=GPIO_Input
PC9.GPIOParameters=GPIO_Label
PC9.GPIO_Label=RELAY_ENABLE
PC9.Signal=GPIO_Output
PD0-OSC_IN.Mode=HSE-External-Oscillator
PD0-OSC_IN.Signal=RCC_OSC_IN
PD1-OSC_OUT.Mode=HSE-External-Oscillator
PD1-OSC_OUT.Signal=RCC_OSC_OUT
RCC.SYSCLKFreq_VALUE=64000000
RCC.SYSCLKSource=RCC_SYSCLKSOURCE_PLLCLK
board=NUCLEO-F103RB
boardIOC=true
